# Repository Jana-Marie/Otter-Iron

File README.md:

# Otter-Iron

Replacement PCB for TS100, adds USB-C PD to every hacker's favourite tool!

Hardware v2.4 is released, changelog: you don't need to solder the tip connector anymore, software [v0.6](https://github.com/Jana-Marie/Otter-Iron/releases) is released!

Features:
 - You can solder!
 - Temperature can be adjusted via buttons
 - USB-PD requests highest voltage
 - Display shows set-temperature, temperature, input-voltage and power applied
 - Saves last set-temperature
 - Designed by an Otter *chirps* :3

## Ordering and assembly instructions

The BOM can be found at [KiCAD/Otter-Iron/production/kitspace_bom.csv](./KiCAD/Otter-Iron/production/kitspace_bom.csv). Most parts are generic parts, which can be ordered and assembled regularly. However, the display and tip-holders need special attention. The PCB has to be ordered with a thickness of 1mm (1.6mm works too, but 1mm has a better fit).

### Known hardware issues/notes

 * **Note: C19 and C20 changed from 100nF to 1µF in the last revision, please make sure to populate 1µF!**
 * Please add a pullup to the displays reset if the display does not work. See image below:

### Tip-Holders / mechanical parts

The original tip-holders are custom made thus it is not possible to buy them, if you already have a TS100 it is highly recommended to recycle those. They can be unscrewed, cut to size and soldered/screwed onto the Otter-Iron. This is the preferred option!

If you don't own a TS100 you can buy one from miniware (price ranges from 35$ to 45$) and harvest the parts (as well as the casing and tip!).

You can also buy the littlefuse fuseholders mentioned in the BOM. Those however have a very bad fit, you have to bend them and add a little solder notch, otherwise you may destroy your tips. In addition to this solution you also need to buy a spare case+tip which is ~25-35$, this is the least preferred option.

### Display

The display can be bought from ~~[LCSC](https://lcsc.com/product-detail/OLED-Displays-Modules_UG-Univision-Semicon-UG-9616TSWCG02_C88335.html)~~ **note: Do not buy displays from LCSC, they seem to be faulty!** or [Aliexpress](https://de.aliexpress.com/item/32808645444.html), I haven't found it at Mouser yet ([Maybe its this display?](https://www.mouser.de/ProductDetail/ELECTRONIC-ASSEMBLY/EA-W096016-XALW?qs=f9yNj16SXrJLTMk24BHqcA%3D%3D)). It is the last part to be assembled, it is soldered on the back of the PCB facing the PCB and the tip-end.

## Flashing

To flash the Otter-Iron short the DFU-jumper shown in the image below while plugging it into your computer. This will put the iron into DFU mode allowing you to flash it via DFU/USB.

If you already have ad firmware >= v0.2 flashed, you can press both buttons while plugging in to enter DFU mode.

Run this command to flash the downloaded binary.

    $ dfu-util -a 0 -s 0x08000000:leave -D firmware.bin

## Video

## Images

## Todo software

 - [x] Write a better regulation
 - [x] Current measurement
 - [x] Store last setpoint
 - [x] Better Fonts/UI
 - [x] PD-Profile cycling

## Todo Hardware

Todo next hardware revision:
 - [ ] Add barrel jack
 - [ ] Add grounding solution
 - [x] Fix Tag-Connect [see #4](https://github.com/Jana-Marie/Otter-Iron/issues/4)
 - [x] Optimize display-connector
 - [x] Add display reset pullup
 - [ ] Add display reset line
 - [ ] Add inrush current protection

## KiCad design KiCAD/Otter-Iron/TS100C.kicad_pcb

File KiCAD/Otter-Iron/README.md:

[BOM](KiCAD/production/kitspace_bom.csv)

[Gerber](KiCAD/production/TS100CV2.3.zip)

[Kitspace](https://kitspace.org/boards/github.com/jana-marie/otter-iron/)

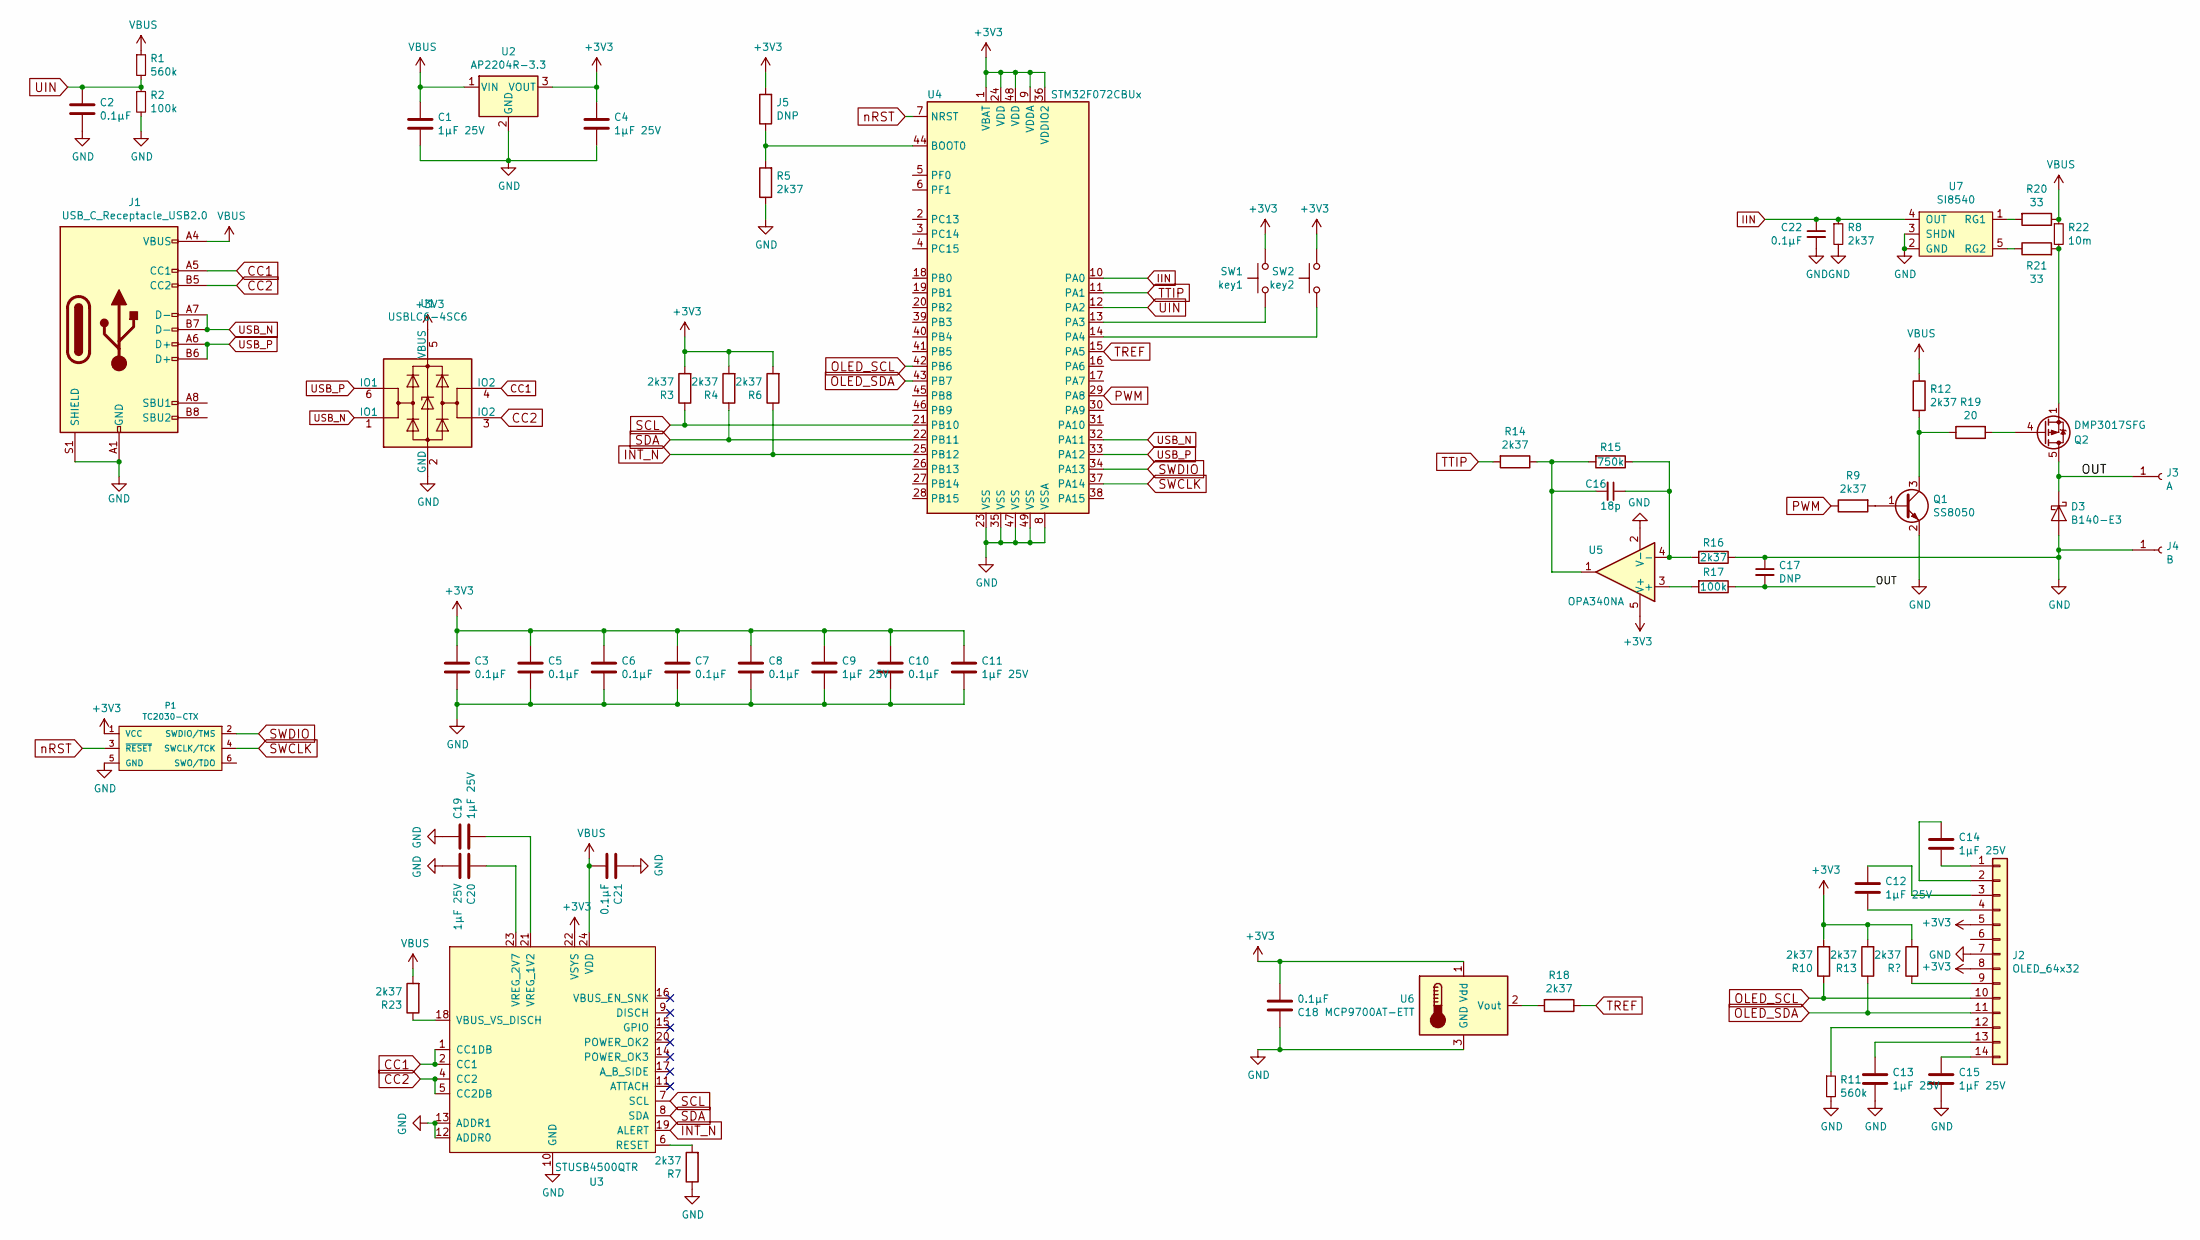
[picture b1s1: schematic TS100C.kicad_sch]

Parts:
C1, C4, C9, C11: 1μF 25V; C_0603_1608Metric
C2, C3, C5, C6, C7, C8, C10, C18, C21, C22: 0.1μF; C_0402_1005Metric
C12, C13, C14, C15, C19, C20: 1μF 25V; C_0402_1005Metric
C16: 18p; C_0402_1005Metric
C17: DNP; C_0402_1005Metric
D3: B140-E3; D_SOD-123F
J1: USB_C_Receptacle_USB2.0; USB-C 16Pin
J2: OLED_64x32; 0.69OLED
J3: A; Keystone_3621
J4: B; 3622TR
J5: DNP; R_0402_1005Metric
P1: TC2030-CTX; TC2030-NL_SMALL
Q1: SS8050; SOT-23
Q2: DMP3017SFG; Diodes_PowerDI3333-8
R1, R11: 560k; R_0402_1005Metric
R2, R17: 100k; R_0402_1005Metric
R3, R4, R5, R6, R7, R8, R9, R10, R12, R13, R14, R16, R18, R23: 2k37; R_0402_1005Metric
R15: 750k; R_0402_1005Metric
R19: 20; R_0402_1005Metric
R20, R21: 33; R_0402_1005Metric
R22: 10m; R_0805_2012Metric
SW1: key1; SW_SPST_PTS810
SW2: key2; SW_SPST_PTS810
U1: USBLC6-4SC6; SOT-23-6
U2: AP2204R-3.3; SOT-89-3
U3: STUSB4500QTR; QFN-24-1EP_4x4mm_P0.5mm_EP2.7x2.7mm
U4: STM32F072CBUx; QFN-48-1EP_7x7mm_P0.5mm_EP5.6x5.6mm
U5: OPA340NA; SOT-23-5
U6: MCP9700AT-ETT; SOT-23
U7: SI8540; SOT-23-5

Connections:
+3V3: C3.1, C4.1, C5.1, C6.1, C7.1, C8.1, C9.1, C10.1, C11.1, C18.1, J2.5, J2.8, J5.2, P1.1 (VCC), R3.2, R4.2, R6.2, R10.2, R13.2, SW1.1, SW2.1, U1.5 (VBUS), U2.3 (VOUT), U3.22 (VSYS), U4.1 (VBAT), U4.9 (VDDA), U4.24 (VDD), U4.36 (VDDIO2), U4.48 (VDD), U5.5 (V+), U6.1 (Vdd); also elsewhere on the board
/OUT: C17.2, D3.1 (K), J3.1, Q2.5 (D), R17.1
CC1: J1.A5 (CC1), U1.4 (IO2), U3.1 (CC1DB), U3.2 (CC1)
CC2: J1.B5 (CC2), U1.3 (IO2), U3.4 (CC2), U3.5 (CC2DB)
GND: C1.2, C2.2, C3.2, C4.2, C5.2, C6.2, C7.2, C8.2, C9.2, C10.2, C11.2, C13.2, C15.2, C17.1, C18.2, C19.1, C20.2, C21.1, C22.2, D3.2 (A), J1.A1 (GND), J1.A12 (GND), J1.B1 (GND), J1.B12 (GND), J1.S1 (SHIELD), J2.7, J4.1, P1.5 (GND), Q1.2 (E), R2.2, R5.1, R7.1, R8.2, R11.2, R16.1, U1.2 (GND), U2.2 (GND), U3.10 (GND), U3.12 (ADDR0), U3.13 (ADDR1), U3.25 (GND), U4.8 (VSSA), U4.23 (VSS), U4.35 (VSS), U4.47 (VSS), U4.49 (VSS), U5.2 (V-), U6.3 (GND), U7.2 (GND), U7.3 (SHDN)
IIN: C22.1, R8.1, U4.10 (PA0), U7.4 (OUT)
INT_N: R6.1, U3.19 (ALERT), U4.25 (PB12)
unnamed: C12.1, J2.3
unnamed: C12.2, J2.4
unnamed: C13.1, J2.13
unnamed: C14.1, J2.2
unnamed: C14.2, J2.1
unnamed: C15.1, J2.14
unnamed: C16.1, R15.1, R16.2, U5.4 (-)
unnamed: C16.2, R14.1, R15.2, U5.1
unnamed: C19.2, U3.21 (VREG_1V2)
unnamed: C20.1, U3.23 (VREG_2V7)
unnamed 20: J2.9; also elsewhere on the board
unnamed: J2.12, R11.1
unnamed: J5.1, R5.2, U4.44 (BOOT0)
unnamed: Q1.1 (B), R9.2
unnamed: Q1.3 (C), R12.2, R19.1
unnamed: Q2.1 (S), Q2.2 (S), Q2.3 (S), R21.2, R22.2
unnamed: Q2.4 (G), R19.2
unnamed: R7.2, U3.6 (RESET)
unnamed: R17.2, U5.3 (+)
unnamed: R18.2, U6.2 (Vout)
unnamed: R20.2, U7.1 (RG1)
unnamed: R21.1, U7.5 (RG2)
unnamed: R23.1, U3.18 (VBUS_VS_DISCH)
unnamed: SW1.2, U4.13 (PA3)
unnamed: SW2.2, U4.14 (PA4)
OLED_SCL: J2.10, R10.1, U4.42 (PB6)
OLED_SDA: J2.11, R13.1, U4.43 (PB7)
PWM: R9.1, U4.29 (PA8)
SCL: R3.1, U3.7 (SCL), U4.21 (PB10)
SDA: R4.1, U3.8 (SDA), U4.22 (PB11)
SWCLK: P1.4 (SWCLK/TCK), U4.37 (PA14)
SWDIO: P1.2 (SWDIO/TMS), U4.34 (PA13)
TREF: R18.1, U4.15 (PA5)
TTIP: R14.2, U4.11 (PA1)
UIN: C2.1, R1.2, R2.1, U4.12 (PA2)
USB_N: J1.A7 (D-), J1.B7 (D-), U1.1 (IO1), U4.32 (PA11)
USB_P: J1.A6 (D+), J1.B6 (D+), U1.6 (IO1), U4.33 (PA12)
VBUS: C1.1, C21.2, J1.A4 (VBUS), J1.A9 (VBUS), J1.B4 (VBUS), J1.B9 (VBUS), R1.1, R12.1, R20.1, R22.1, R23.2, U2.1 (VIN), U3.24 (VDD)
nRST: P1.3 (~RESET), U4.7 (NRST)

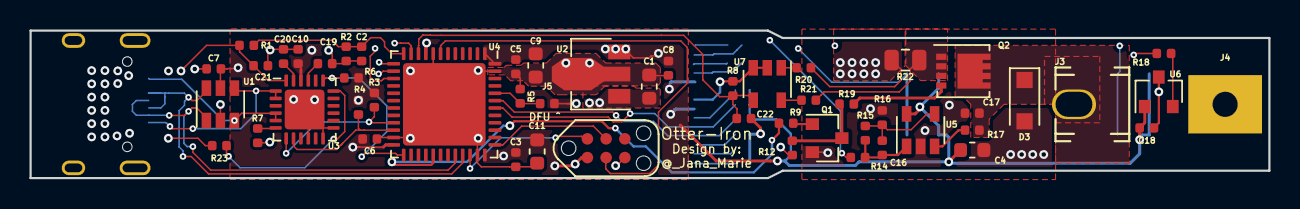
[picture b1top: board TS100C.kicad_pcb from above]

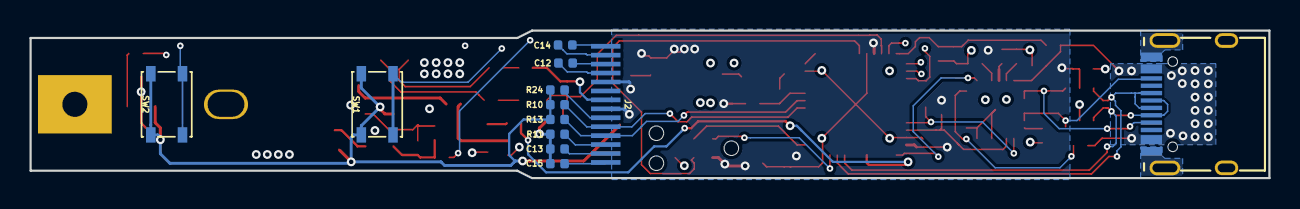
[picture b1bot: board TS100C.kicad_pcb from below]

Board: 4 copper layers, 84.0 x 10.0 mm, 64 parts (12 on the bottom side), 46 nets.

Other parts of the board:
R24: 2k37; R_0402_1005Metric

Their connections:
+3V3: R24.2; also elsewhere on the board
unnamed 20: R24.1; also elsewhere on the board

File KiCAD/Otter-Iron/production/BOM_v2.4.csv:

Comment,Designator,Quantity,Footprint,LCSC,LCSC Part type,Mouser,Farnell 
1μF 25V,"C15,C13,C14,C12,C20,C19",6,Capacitor_SMD:C_0402_1005Metric,C52923,smt,,
18p,C16,1,Capacitor_SMD:C_0402_1005Metric,C1549,smt,,
DNP,C17,1,Capacitor_SMD:C_0402_1005Metric,DNP,dnp,,
0.1μF,"C3,C5,C7,C8,C10,C2,C18,C6,C21,C22",10,Capacitor_SMD:C_0402_1005Metric,C1525,smt,,
1μF 25V,"C9,C1,C4,C11",4,Capacitor_SMD:C_0603_1608Metric,C15849,smt,,
B140-E3,D3,1,Diode_SMD:D_SOD-123F,C64891,ext,,
USB_C_Receptacle_USB2.0,J1,1,otter:USB-C 16Pin,C319148,lcsc,,
OLED_96x16,J2,1,otter:0.69OLED,,,,
A,J3,1,otter:Keystone_3621,,,534-3621 ,
B,J4,1,otter:Keystone_3622,,,534-3622,
DNP,J5,1,Resistor_SMD:R_0402_1005Metric,DNP,dnp,,
SS8050,Q1,1,Package_TO_SOT_SMD:SOT-23,C2150,smt,,
DMP3017SFG,Q2,1,otter:Diodes_PowerDI3333-8,C461072,lcsc,,
560k,"R1,R11",2,Resistor_SMD:R_0402_1005Metric,C132339,ext,,
750k,R15,1,Resistor_SMD:R_0402_1005Metric,C122545,ext,,
20,R19,1,Resistor_SMD:R_0402_1005Metric,C25089,ext,,
100k,"R2,R17",2,Resistor_SMD:R_0402_1005Metric,C25741,smt,,
33,"R20,R21",2,Resistor_SMD:R_0402_1005Metric,C25105,smt,,
10m,R22,1,Resistor_SMD:R_0805_2012Metric,C50732,ext,,
2k37,"R5,R3,R4,R6,R12,R9,R10,R13,R16,R14,R18,R7,R8,R23",14,Resistor_SMD:R_0402_1005Metric,C25881,ext,,
key1,SW1,1,Button_Switch_SMD:SW_SPST_PTS810,C92589,lcsc,,
key2,SW2,1,Button_Switch_SMD:SW_SPST_PTS810,C92589,lcsc,,
USBLC6-4SC6,U1,1,Package_TO_SOT_SMD:SOT-23-6,C111212,ext,,1295311
AP2204R-3.3,U2,1,Package_TO_SOT_SMD:SOT-89-3,C156303,ext,,
STUSB4500QTR,U3,1,Package_DFN_QFN:QFN-24-1EP_4x4mm_P0.5mm_EP2.7x2.7mm,,,511-STUSB4500QTR ,2980889
STM32F072CBUx,U4,1,Package_DFN_QFN:QFN-48-1EP_7x7mm_P0.5mm_EP5.6x5.6mm,C92504,ext,,
OPA340NA,U5,1,Package_TO_SOT_SMD:SOT-23-5,C73479,ext,,
MCP9700AT-ETT,U6,1,Package_TO_SOT_SMD:SOT-23,,,579-MCP9700AT-E/TT,1605577
SI8540,U7,1,Package_TO_SOT_SMD:SOT-23-5,,,634-SI8540-B-FWR ,SI8540

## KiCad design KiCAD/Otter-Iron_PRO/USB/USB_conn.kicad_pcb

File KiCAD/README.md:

# Folder structure

## Otter-Iron

Replacement PCB for the TS100.

## Otter-Iron_Devkit

Small devboard based on the Otter-Iron for different tips (e.g. Weller RT, JBC C245)

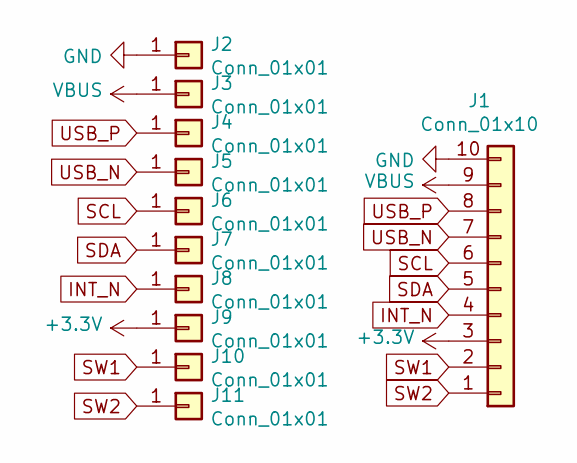
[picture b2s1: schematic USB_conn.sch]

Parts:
J1: Conn_01x10; PinHeader_1x10_P2.00mm_Vertical
J2, J3: Conn_01x01; pad_1.5_3
J4, J5: Conn_01x01; pad_0.75_3
J6, J7, J8, J9, J10, J11: Conn_01x01; pad_1_2

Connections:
+3V3: J1.3, J9.1
GND: J1.10, J2.1
INT_N: J1.4, J8.1
SCL: J1.6, J6.1
SDA: J1.5, J7.1
SW1: J1.2, J10.1
SW2: J1.1, J11.1
USB_N: J1.7, J5.1
USB_P: J1.8, J4.1
VBUS: J1.9, J3.1

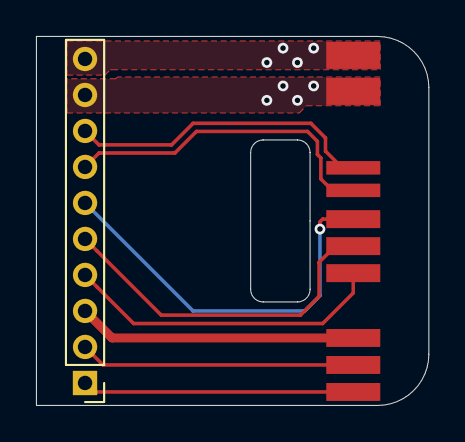
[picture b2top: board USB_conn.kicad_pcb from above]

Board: 2 copper layers, 21.8 x 20.5 mm, 11 parts (0 on the bottom side), 10 nets.

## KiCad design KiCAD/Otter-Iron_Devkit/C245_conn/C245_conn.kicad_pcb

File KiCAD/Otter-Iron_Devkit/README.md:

Moved to new repo: [https://github.com/Jan--Henrik/Otter-Iron-PRO](https://github.com/Jan--Henrik/Otter-Iron-PRO)

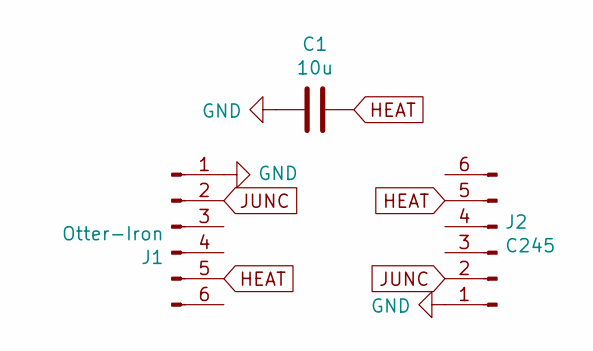
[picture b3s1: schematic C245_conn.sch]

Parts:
C1: 10u; C_1206_3216Metric
J1: Otter-Iron; PinHeader_1x06_P2.54mm_Vertical
J2: C245; RPC1-12RB-6P(71)

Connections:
GND: C1.2, J1.1, J2.1
HEAT: C1.1, J1.5, J2.5
JUNC: J1.2, J2.2

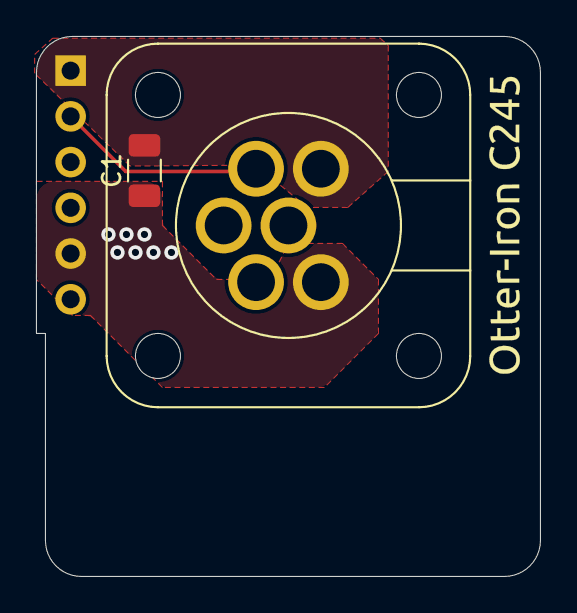
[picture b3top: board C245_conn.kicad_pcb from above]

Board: 2 copper layers, 28.0 x 30.0 mm, 3 parts (1 on the bottom side), 3 nets.

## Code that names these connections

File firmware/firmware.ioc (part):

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Mcu.Name=STM32F072C(8-B)Ux
Mcu.Package=UFQFPN48
Mcu.UserName=STM32F072CBUx
PA0.GPIOParameters=GPIO_Label
PA0.GPIO_Label=IIN
PA0.Mode=IN0
PA0.Signal=ADC_IN0
PA1.GPIOParameters=GPIO_Label
PA1.GPIO_Label=TTIP
PA1.Mode=IN1
PA1.Signal=ADC_IN1
PA11.Mode=Device
PA11.Signal=USB_DM
PA12.Mode=Device
PA12.Signal=USB_DP
PA13.Mode=Serial_Wire
PA13.Signal=SYS_SWDIO
PA14.Mode=Serial_Wire
PA14.Signal=SYS_SWCLK
PA2.GPIOParameters=GPIO_Label
PA2.GPIO_Label=UIN
PA2.Mode=IN2
PA2.Signal=ADC_IN2
PA3.GPIOParameters=GPIO_Label
PA3.GPIO_Label=B1
PA3.Signal=GPIO_Input
PA4.GPIOParameters=GPIO_Label
PA4.GPIO_Label=B2
PA4.Signal=GPIO_Input
PA5.GPIOParameters=GPIO_Label
PA5.GPIO_Label=TREF
PA5.Mode=IN5
PA5.Signal=ADC_IN5
PB10.GPIOParameters=GPIO_Label
PB10.GPIO_Label=STUSB_SCL
PB10.Mode=I2C
PB10.Signal=I2C2_SCL
PB11.GPIOParameters=GPIO_Label
PB11.GPIO_Label=STUSB_SDA
PB11.Mode=I2C
PB11.Signal=I2C2_SDA
PB12.GPIOParameters=GPIO_Label
PB12.GPIO_Label=INT_N
PB12.Signal=GPIO_Input
PB3.GPIOParameters=GPIO_Label
PB3.GPIO_Label=PWMOUT
PB3.Signal=S_TIM2_CH2
PB6.GPIOParameters=GPIO_Label
PB6.GPIO_Label=OLED_SCL
PB6.Mode=I2C
PB6.Signal=I2C1_SCL
PB7.GPIOParameters=GPIO_Label
PB7.GPIO_Label=OLED_SDA
PB7.Mode=I2C
PB7.Signal=I2C1_SDA
RCC.SYSCLKFreq_VALUE=48000000
RCC.SYSCLKSource=RCC_SYSCLKSOURCE_PLLCLK
board=custom

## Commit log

2018-11-08 initital commit
2018-11-08 added kicad files
2018-11-08 added ioc file
2018-11-08 added most parts
2018-11-08 update PCB
2018-11-09 finalized PCB
2018-11-09 added images
2018-11-09 added issue
2018-11-09 fixed connector error
2018-12-04 updated files
2018-12-05 Create LICENSE
2018-12-09 file cleanup
2018-12-09 moved files
2019-05-22 removed gerber
2019-05-22 added new gerber
2019-05-22 updated PCB+schematic to STUSB4500
2019-05-22 updated images
2019-05-22 added silkscreen
2019-07-16 updated pcb
2019-07-24 added gitignore
2019-07-24 added firmware
2019-07-24 updated hardware
2019-07-24 added todos
2019-07-24 worked on firmware, hardware init mostly done
2019-08-13 fixed bom
2019-08-13 optimized bom
2019-08-21 optimized values
2019-08-29 TIM1 PWM + ADC Trigger -> DMA works
2019-08-29 backup
2019-09-03 added BOM
2019-12-17 fixed STM
2019-12-22 fixed controller
2019-12-22 v0.1
2019-12-22 removed old images
2019-12-23 removed old stuff
2019-12-23 added firmware release 0.1
2019-12-23 removed old files
2019-12-23 production files
2019-12-23 added dfu image
2019-12-24 Add kitspace.yaml
2019-12-24 Make a kitspace compatible bom
    Delete some rows/columns from production/BOM.csv
2019-12-31 updated kitspace bom
2019-12-31 updated bom
2020-01-03 updated cap values
2020-01-03 added dfu bootloader
2020-01-03 added dfu bootloader & cascaded controller
2020-01-03 added code comments
2020-01-15 updated DFU screen, TS100 stores now set-temp, highly improved temperature control
2020-01-15 updated bins
2020-01-15 removed binaries
2020-01-15 added thumbnail
2020-01-15 fixed power-bar bug
2020-01-21 added image
2020-01-21 removed old file
2020-01-21 optimized TC & Display connector, added pullup
2020-01-28 fixed cpl file bugs
2020-02-04 fixed initial temp set
2020-02-05 added USB CDC
2020-02-05 corrected spelling err
2020-02-05 added watchdog
2020-02-05 fixed critical bug
2020-02-10 Upadeted BOM.csv with Farnell#
    Added Farnell ordering numbers for non-LCSC parts
2020-02-10 merged boms
2020-03-01 added C245_Test
2020-03-01 finished routing C245_Test
2020-03-01 finalized design
2020-03-01 added connector pcb, added Gerber
2020-03-01 added connector, renamed files
2020-03-01 renamed files
2020-03-01 moved folder
2020-03-01 added gerber zip
2020-03-02 fixed some typos
2020-03-03 moved serial com to define
2020-03-03 extended gitignore
2020-04-12 added current monitoring and current control, added devkit fw
2020-04-12 added v2.0
2020-04-13 added Otter-Iron PRO
2020-04-13 added PRO
2020-04-13 updated production files
2020-04-15 moved files to new repo
2020-04-17 added pdf
2020-06-23 fix BOM link
2020-09-30 Update README.md
    updated readme
2020-10-25 updated display and PD firmware
2020-10-26 added 12V and 9V profile
2022-01-09 hw v2.4 released
2022-01-09 added names
2022-01-09 updated gitignore
